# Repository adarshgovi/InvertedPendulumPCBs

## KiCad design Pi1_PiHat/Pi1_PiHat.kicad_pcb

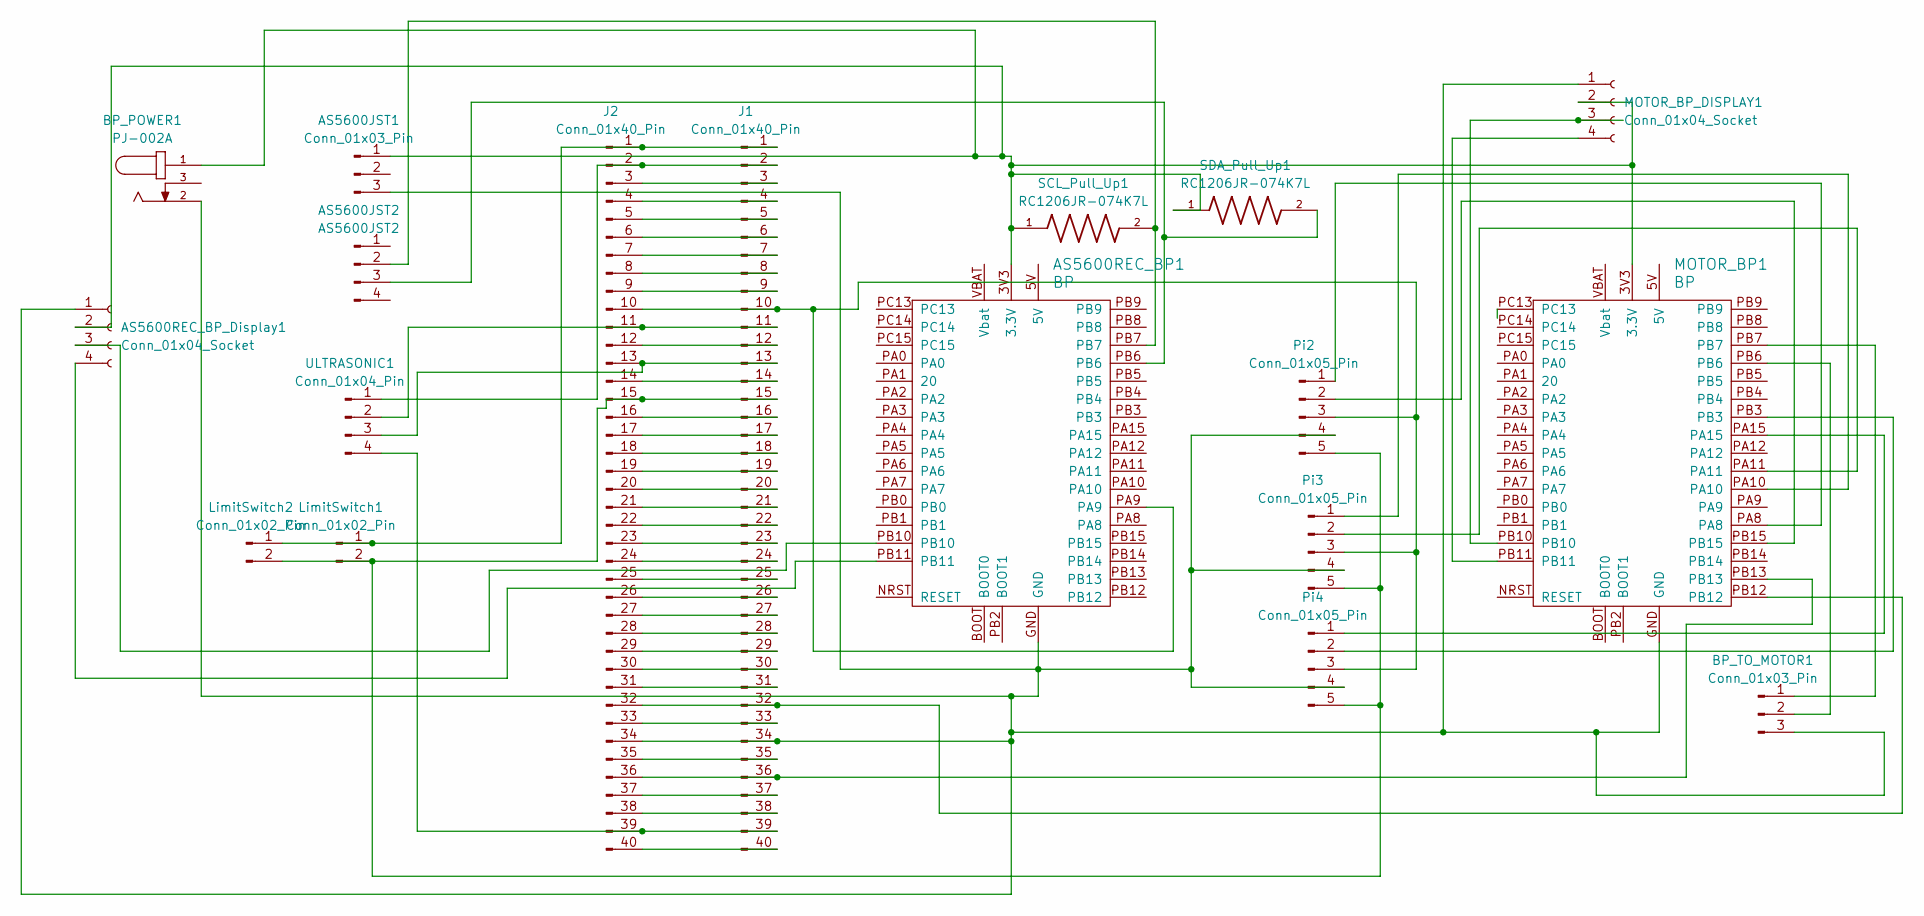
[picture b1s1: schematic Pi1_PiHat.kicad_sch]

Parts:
AS5600JST1: Conn_01x03_Pin; JST_EH_B3B-EH-A_1x03_P2.50mm_Vertical
AS5600JST2: AS5600JST2; JST_EH_B4B-EH-A_1x04_P2.50mm_Vertical
AS5600REC_BP1: BP; ChinaBluePill
AS5600REC_BP_Display1: Conn_01x04_Socket; PinSocket_1x04_P2.54mm_Vertical
BP_POWER1: PJ-002A; CUI_PJ-002A; DigiKey_Part_Number CP-002A-ND
BP_TO_MOTOR1: Conn_01x03_Pin; JST_EH_B3B-EH-A_1x03_P2.50mm_Vertical
J1, J2: Conn_01x40_Pin; TE_7-146256-0
LimitSwitch1, LimitSwitch2: Conn_01x02_Pin; JST_EH_B2B-EH-A_1x02_P2.50mm_Vertical
MOTOR_BP1: BP; ChinaBluePill
MOTOR_BP_DISPLAY1: Conn_01x04_Socket; PinSocket_1x04_P2.54mm_Vertical
Pi2, Pi3, Pi4: Conn_01x05_Pin; JST_EH_B5B-EH-A_1x05_P2.50mm_Vertical
SCL_Pull_Up1: RC1206JR-074K7L; RESC3116X65N; DigiKey_Part_Number 311-4.7KERTR-ND
SDA_Pull_Up1: RC1206JR-074K7L; RESC3116X65N; DigiKey_Part_Number 311-4.7KERTR-ND
ULTRASONIC1: Conn_01x04_Pin; JST_EH_B4B-EH-A_1x04_P2.50mm_Vertical

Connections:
unnamed: AS5600JST1.1, AS5600REC_BP1.3V3 (3.3V), AS5600REC_BP_Display1.2, BP_POWER1.1, MOTOR_BP1.3V3 (3.3V), MOTOR_BP_DISPLAY1.2, SCL_Pull_Up1.1, SDA_Pull_Up1.1
unnamed: AS5600JST1.3, AS5600REC_BP1.GND, AS5600REC_BP_Display1.1, BP_POWER1.2, BP_TO_MOTOR1.3, J1.34, J2.34, MOTOR_BP1.GND, MOTOR_BP_DISPLAY1.1, Pi2.4, Pi3.4, Pi4.4
unnamed: AS5600JST2.2, AS5600REC_BP1.PB7, SCL_Pull_Up1.2
unnamed: AS5600JST2.3, AS5600REC_BP1.PB6, SDA_Pull_Up1.2
unnamed: AS5600REC_BP1.PB10, AS5600REC_BP_Display1.3
unnamed: AS5600REC_BP1.PB11, AS5600REC_BP_Display1.4
unnamed: BP_TO_MOTOR1.1, MOTOR_BP1.PB7
unnamed: BP_TO_MOTOR1.2, MOTOR_BP1.PB6
unnamed: J1.1, J2.1, LimitSwitch1.1, LimitSwitch2.1
unnamed: J1.2, J2.2, ULTRASONIC1.1
unnamed: J1.3, J2.3
unnamed: J1.4, J2.4
unnamed: J1.5, J2.5
unnamed: J1.6, J2.6
unnamed: J1.7, J2.7
unnamed: J1.8, J2.8
unnamed: J1.9, J2.9
unnamed: AS5600REC_BP1.PA9, J1.10, J2.10, Pi2.3, Pi3.3, Pi4.3
unnamed: J1.11, J2.11, ULTRASONIC1.2
unnamed: J1.12, J2.12
unnamed: J1.13, J2.13, ULTRASONIC1.3
unnamed: J1.14, J2.14
unnamed: J1.15, J2.15, LimitSwitch1.2, LimitSwitch2.2, Pi2.5, Pi3.5, Pi4.5
unnamed: J1.16, J2.16
unnamed: J1.17, J2.17
unnamed: J1.18, J2.18
unnamed: J1.19, J2.19
unnamed: J1.20, J2.20
unnamed: J1.21, J2.21
unnamed: J1.22, J2.22
unnamed: J1.23, J2.23
unnamed: J1.24, J2.24
unnamed: J1.25, J2.25
unnamed: J1.26, J2.26
unnamed: J1.27, J2.27
unnamed: J1.28, J2.28
unnamed: J1.29, J2.29
unnamed: J1.30, J2.30
unnamed: J1.31, J2.31
unnamed: J1.32, J2.32, MOTOR_BP1.PB12
unnamed: J1.33, J2.33
unnamed: J1.35, J2.35
unnamed: J1.36, J2.36, MOTOR_BP1.PB13
unnamed: J1.37, J2.37
unnamed: J1.38, J2.38
unnamed: J1.39, J2.39, ULTRASONIC1.4
unnamed: J1.40, J2.40
unnamed: MOTOR_BP1.PB10, MOTOR_BP_DISPLAY1.3
unnamed: MOTOR_BP1.PB11, MOTOR_BP_DISPLAY1.4
unnamed: MOTOR_BP1.PA8, Pi2.1
unnamed: MOTOR_BP1.PB15, Pi2.2
unnamed: MOTOR_BP1.PA10, Pi3.1
unnamed: MOTOR_BP1.PA11, Pi3.2
unnamed: MOTOR_BP1.PA15, Pi4.1
unnamed: MOTOR_BP1.PB3, Pi4.2

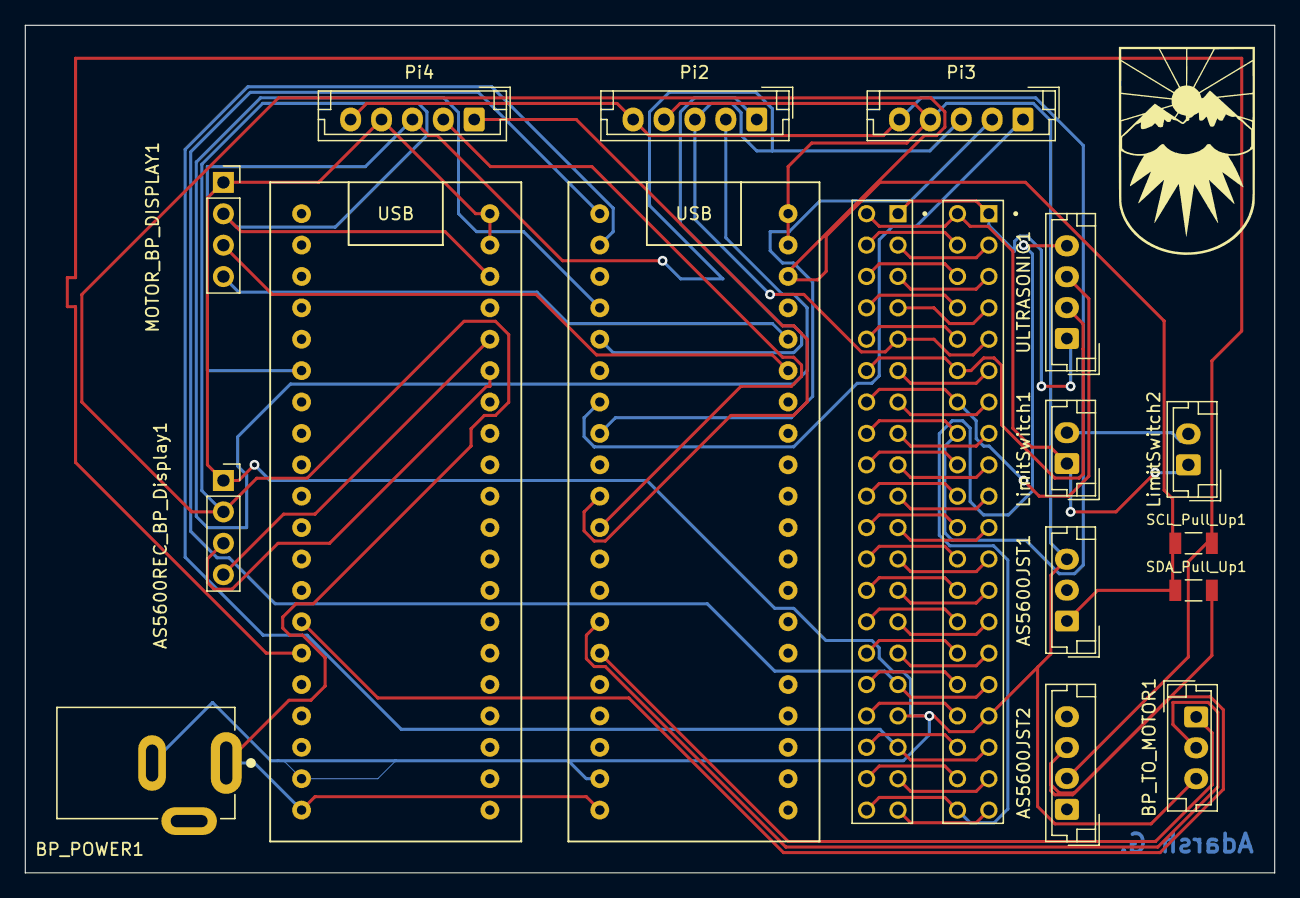
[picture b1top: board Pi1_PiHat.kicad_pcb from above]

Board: 2 copper layers, 101.1 x 68.6 mm, 18 parts (0 on the bottom side), 55 nets.

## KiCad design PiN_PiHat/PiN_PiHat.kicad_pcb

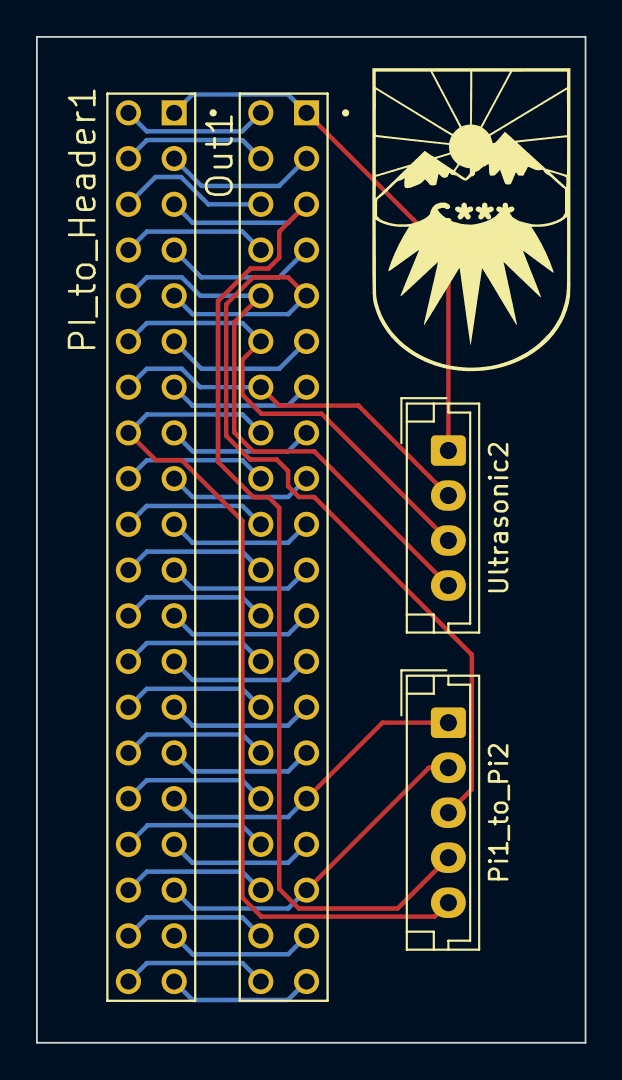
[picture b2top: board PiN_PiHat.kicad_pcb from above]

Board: 2 copper layers, 30.5 x 55.9 mm, 4 parts (0 on the bottom side), 40 nets.

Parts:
Out1: Conn_01x40_Pin; TE_7-146256-0
PI_to_Header1: Conn_01x40_Pin; TE_7-146256-0
Pi1_to_Pi2: Conn_01x05_Pin; JST_EH_B5B-EH-A_1x05_P2.50mm_Vertical
Ultrasonic2: Conn_01x04_Pin; JST_EH_B4B-EH-A_1x04_P2.50mm_Vertical

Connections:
unnamed: Out1.1, PI_to_Header1.1
unnamed: Out1.2, PI_to_Header1.2, Ultrasonic2.1
unnamed: Out1.3, PI_to_Header1.3
unnamed: Out1.4, PI_to_Header1.4
unnamed: Out1.5, PI_to_Header1.5
unnamed: Out1.6, PI_to_Header1.6, Pi1_to_Pi2.4
unnamed: Out1.7, PI_to_Header1.7
unnamed: Out1.8, PI_to_Header1.8
unnamed: Out1.9, PI_to_Header1.9, Ultrasonic2.4
unnamed: Out1.10, PI_to_Header1.10, Pi1_to_Pi2.3
unnamed: Out1.11, PI_to_Header1.11, Ultrasonic2.3
unnamed: Out1.12, PI_to_Header1.12
unnamed: Out1.13, PI_to_Header1.13, Ultrasonic2.2
unnamed: Out1.14, PI_to_Header1.14
unnamed: Out1.15, PI_to_Header1.15, Pi1_to_Pi2.5
unnamed: Out1.16, PI_to_Header1.16
unnamed: Out1.17, PI_to_Header1.17
unnamed: Out1.18, PI_to_Header1.18
unnamed: Out1.19, PI_to_Header1.19
unnamed: Out1.20, PI_to_Header1.20
unnamed: Out1.21, PI_to_Header1.21
unnamed: Out1.22, PI_to_Header1.22
unnamed: Out1.23, PI_to_Header1.23
unnamed: Out1.24, PI_to_Header1.24
unnamed: Out1.25, PI_to_Header1.25
unnamed: Out1.26, PI_to_Header1.26
unnamed: Out1.27, PI_to_Header1.27
unnamed: Out1.28, PI_to_Header1.28
unnamed: Out1.29, PI_to_Header1.29
unnamed: Out1.30, PI_to_Header1.30
unnamed: Out1.31, PI_to_Header1.31
unnamed: Out1.32, PI_to_Header1.32, Pi1_to_Pi2.1
unnamed: Out1.33, PI_to_Header1.33
unnamed: Out1.34, PI_to_Header1.34
unnamed: Out1.35, PI_to_Header1.35
unnamed: Out1.36, PI_to_Header1.36, Pi1_to_Pi2.2
unnamed: Out1.37, PI_to_Header1.37
unnamed: Out1.38, PI_to_Header1.38
unnamed: Out1.39, PI_to_Header1.39
unnamed: Out1.40, PI_to_Header1.40
